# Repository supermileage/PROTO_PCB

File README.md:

# PROTO_PCB_2022
Gas Proto's PCB 2022

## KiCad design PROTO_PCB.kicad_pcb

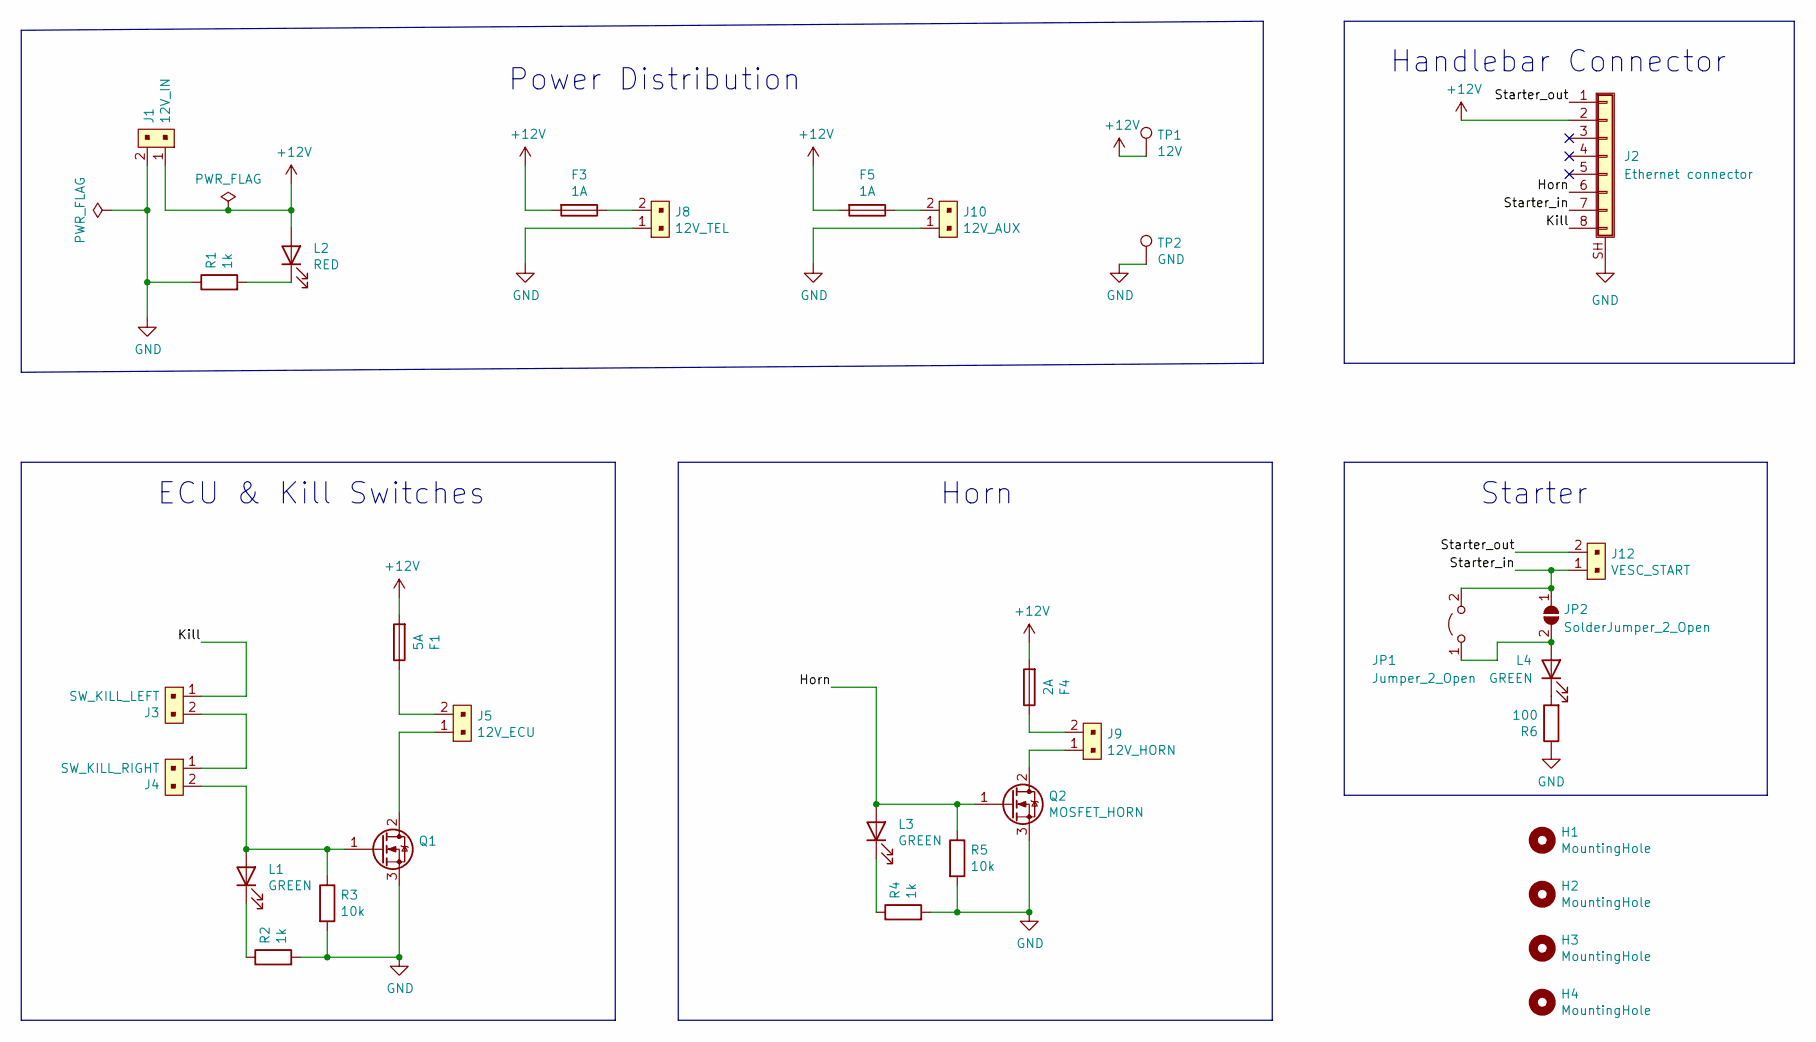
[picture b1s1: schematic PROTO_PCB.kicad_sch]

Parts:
F1: 5A; Fuseholder_Blade_Mini_Keystone_3568
F3, F5: 1A; Fuseholder_Blade_Mini_Keystone_3568
F4: 2A; Fuseholder_Blade_Mini_Keystone_3568
H1, H2, H3, H4: MountingHole; MountingHole_3.2mm_M3
J1: 12V_IN; MOLEX_2002411212
J2: Ethernet connector; RJ45_Amphenol_RJHSE5380
J3: SW_KILL_LEFT; Molex_Micro-Fit_3.0_43650-0200_1x02_P3.00mm_Horizontal
J4: SW_KILL_RIGHT; Molex_Micro-Fit_3.0_43650-0200_1x02_P3.00mm_Horizontal
J5: 12V_ECU; Molex_Micro-Fit_3.0_43650-0200_1x02_P3.00mm_Horizontal
J8: 12V_TEL; Molex_Micro-Fit_3.0_43650-0200_1x02_P3.00mm_Horizontal
J9: 12V_HORN; Molex_Micro-Fit_3.0_43650-0200_1x02_P3.00mm_Horizontal
J10: 12V_AUX; Molex_Micro-Fit_3.0_43650-0200_1x02_P3.00mm_Horizontal
J12: VESC_START; Molex_Micro-Fit_3.0_43650-0200_1x02_P3.00mm_Horizontal
JP1: Jumper_2_Open; PinSocket_1x02_P2.54mm_Vertical
JP2: SolderJumper_2_Open; SolderJumper-2_P1.3mm_Open_TrianglePad1.0x1.5mm
L1, L3, L4: GREEN; LED_1206_3216Metric
L2: RED; LED_1206_3216Metric
Q1: (no value)
Q2: MOSFET_HORN; TO-252-3_TabPin2
R1, R2, R4: 1k; R_1206_3216Metric
R3, R5: 10k; R_1206_3216Metric
R6: 100; R_1206_3216Metric
TP1: 12V; TestPoint_Keystone_5015_Micro-Minature
TP2: GND; TestPoint_Keystone_5015_Micro-Minature

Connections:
+12V: F1.2, F3.2, F4.2, F5.2, J1.1, J2.2, L2.2 (A), TP1.1
/Horn: J2.6, L3.2 (A), Q2.1 (G), R5.1
/Kill: J2.8, J3.1
/Starter_in: J2.7, J12.1, JP1.2 (B), JP2.1 (A)
/Starter_out: J2.1, J12.2
GND: J1.2, J2.SH (Shield), J8.1, J10.1, Q1.3 (S), Q2.3 (S), R1.1, R2.2, R3.2, R4.2, R5.2, R6.1, TP2.1
unnamed: F1.1, J5.2
unnamed: F3.1, J8.2
unnamed: F4.1, J9.2
unnamed: F5.1, J10.2
unnamed: J3.2, J4.1
unnamed: J4.2, L1.2 (A), Q1.1 (G), R3.1
unnamed: J5.1, Q1.2 (D)
unnamed: J9.1, Q2.2 (D)
unnamed: L1.1 (K), R2.1
unnamed: L2.1 (K), R1.2
unnamed: L3.1 (K), R4.1
unnamed: L4.1 (K), R6.2
unnamed: JP1.1 (A), JP2.2 (B), L4.2 (A)

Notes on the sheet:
Horn
Handlebar Connector
Starter
ECU & Kill Switches
Power Distribution

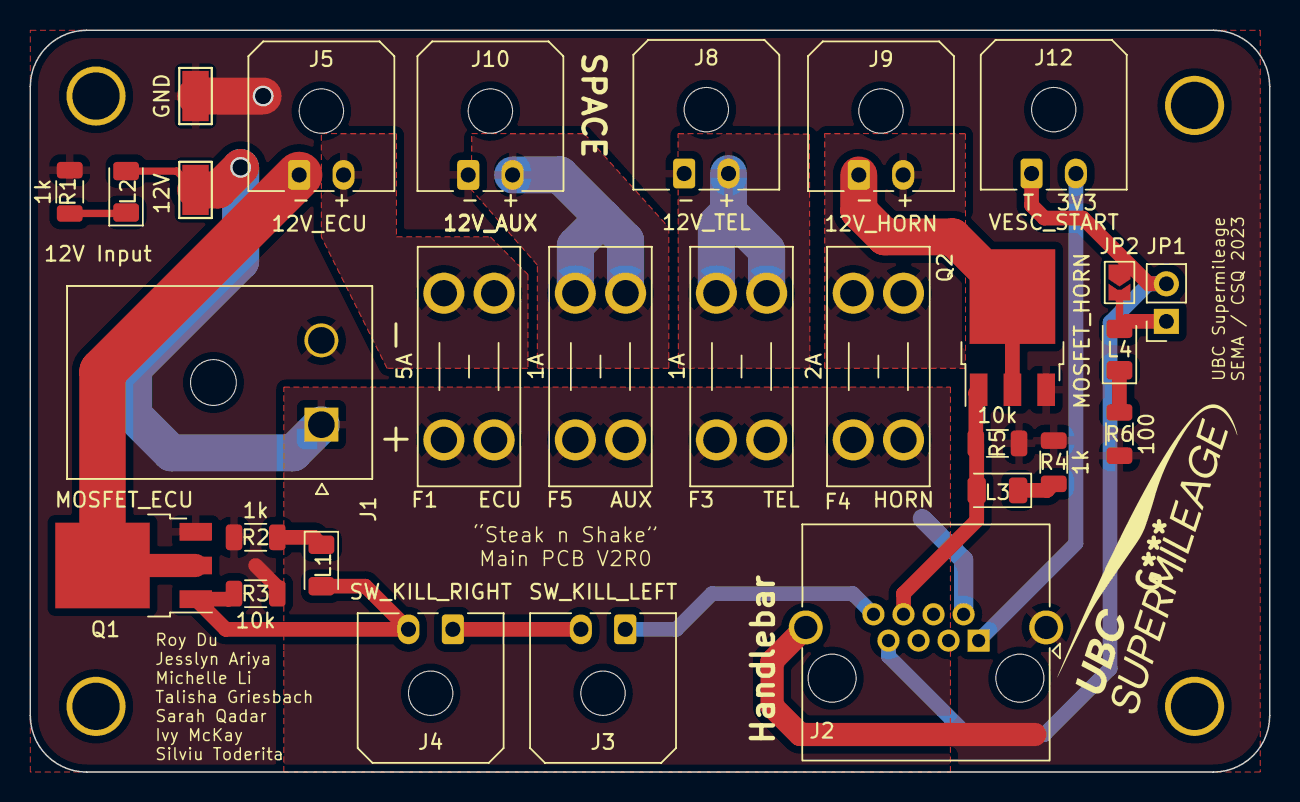
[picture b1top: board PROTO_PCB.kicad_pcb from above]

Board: 2 copper layers, 83.8 x 50.2 mm, 33 parts (0 on the bottom side), 19 nets.

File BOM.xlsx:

Designator | Qty | Manufacturer | Mfg Part # | Description / Value | DigiKey URL
F1,F2,F3,F4,F5 | 5 | Keystone Electronics | 3568 | FUSE HOLDER BLADE 500V 30A PCB | https://www.digikey.ca/en/products/detail/keystone-electroni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
J1 | 1 | Molex | 2002411212 | Connector Header Through Hole, Right Angle 2 position 0.224" (5.70mm) | https://www.digikey.ca/en/products/detail/molex/2002411212/1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
J2,J3,J4,J5,J6,J7,J8,J9,J10,J11,J12 | 11 | Molex | 0436500200 | Connector Header Through Hole, Right Angle 2 position 0.118" (3.00mm) | https://www.digikey.ca/en/products/detail/molex/0436500200/268989
L1,L3,L4 | 3 | Lite-On Inc. | LTST-C230KGKT | LED GREEN CLEAR CHIP SMD | https://www.digikey.ca/en/products/detail/lite-on-inc/LTST-C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
L2 | 1 | Lite-On Inc. | LTST-C230KRKT | LED RED CLEAR CHIP SMD | https://www.digikey.ca/en/products/detail/lite-on-inc/LTST-C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
Q1,Q2 | 2 | Infineon Technologies | IRFR120ZTRPBF | MOSFET N-CH 100V 8.7A DPAK | https://www.digikey.ca/en/products/detail/infineon-technolog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
R1,R2,R4 | 3 | Stackpole Electronics Inc | RMCF1206FT1K00 | RES 1K OHM 1% 1/4W 1206 | https://www.digikey.ca/en/products/detail/stackpole-electron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
R3,R5 | 2 | Stackpole Electronics Inc | RMCF1206FT10K0 | RES 10K OHM 1% 1/4W 1206 | https://www.digikey.ca/en/products/detail/stackpole-electron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
R6 | 1 | Stackpole Electronics Inc | RMCF1206FT100R | RES 100 OHM 1% 1/4W 1206 | https://www.digikey.ca/en/products/detail/stackpole-electron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
Not on PCB:
 | 1 | Molex | 2004561212 | MEGA-FIT RECEP HSG SR TOPL 2CKT | https://www.digikey.ca/en/products/detail/molex/2004561212/10709200
 | 2 | Molex | 0768230344 | MEGA-FIT FEMALE TML PRE-TIN 14/1 | https://www.digikey.ca/en/products/detail/molex/0768230344/10482725
 | 11 | Molex | 0436450200 | CONN RECEPT 2POS 3MM SINGLE ROW | https://www.digikey.ca/en/products/detail/molex/0436450200/268974
 | 22 | Molex | 0430300001 | CONN SOCKET 20-24AWG CRIMP TIN | https://www.digikey.ca/en/products/detail/molex/0430300001/467796
 | 4 |  |  | M3 x 6mm Screws
 | 4 | Littelfuse Inc. | 0297002.L | FUSE AUTO 2A 32VDC BLADE MINI | https://www.digikey.ca/en/products/detail/littelfuse-inc/029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
 | 1 | Littelfuse Inc. | 0297005.WXNV | FUSE AUTO 5A 32VDC BLADE MINI | https://www.digikey.ca/en/products/detail/littelfuse-inc/029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

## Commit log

2022-01-15 Uploading first draft
2022-01-16 Minor changes
2022-01-16 Added ECU molex
2022-01-18 Continued development
2022-01-18 Added footprints/PNs for connectors and updated resistors
2022-01-19 Review and fix power connectors
2022-01-20 Added O2 sensor connector
2022-01-22 Changed power connectors to terminal blocks, updated molex connectors
2022-01-22 Fixed connectors, removed MCU, final first draft
2022-01-22 Updated ECU connector
2022-01-30 replaced 4 pin ECU_EN with 3 2 pin connectors, removed ECU relay and set ECU kill switches in series
2022-03-14 added new TVS diodes to schematic
2022-03-26 board layout done
2022-04-21 layout completed: components arranged, traces created
2022-04-22 Draft PCB for Report Purposes
2022-04-22 second version
2022-04-23 after design review edits start
2022-04-23 changed mosfet
2022-04-24 almost final version
2022-04-25 final design with gerbers
2022-05-11 schematic done
2022-05-11 finished PCB layout
2022-05-12 did some more layout work
2022-05-12 even more layout changes
2022-05-13 finishes schematic, footprint assignment, and BOM
2022-05-13 changed starter LED resistor value from 1k to 100
2022-05-15 new layout
2022-05-15 updates silkscreen and minor tracing
2022-05-15 added some more labels to layout and made BOM doc
2022-05-16 final touch-ups
2023-05-04 small changes: removed brake, added ethernet port
2023-05-14 Changes handlebar connector to RJ45
2023-05-14 Renames files remove year
2023-05-14 VESC connector labels
2023-05-17 2023 pcb
